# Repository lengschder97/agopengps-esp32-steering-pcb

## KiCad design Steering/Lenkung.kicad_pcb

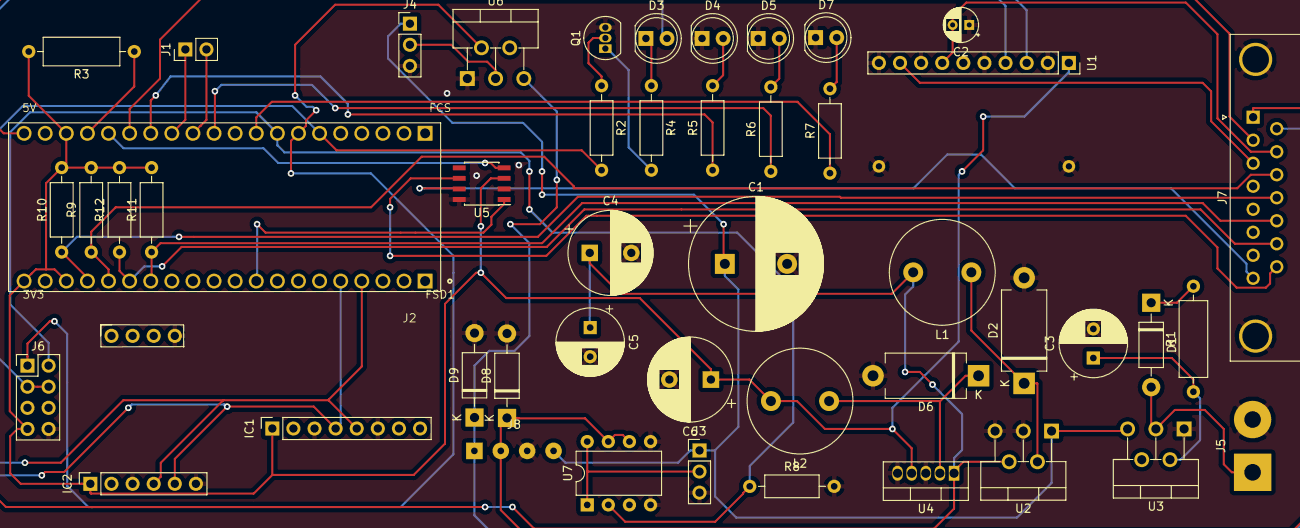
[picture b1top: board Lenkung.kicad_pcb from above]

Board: 2 copper layers, 47 parts (0 on the bottom side), 41 nets.

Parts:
C1: 680µF; CP_Radial_D16.0mm_P7.50mm
C2: 1OµF; CP_Radial_D4.0mm_P2.00mm
C3, C5: 100µF; CP_Radial_D8.0mm_P3.50mm
C4, C6: 220µF; CP_Radial_D10.0mm_P5.00mm
D1, D8, D9: 1N4007; D_DO-41_SOD81_P10.16mm_Horizontal
D2, D6: SB 530; D_DO-201_P12.70mm_Horizontal
D3, D4, D5, D7: LED; LED_D5.0mm
IC1: MMA8452-Board; PinSocket_1x08_P2.54mm_Vertical
IC2: BNO055; PinSocket_1x06_P2.54mm_Vertical-Board
J1: Conn_01x02_Female; PinHeader_1x02_P2.54mm_Vertical
J2: ESP32-PICO-KIT; XCVR_ESP32-PICO-KIT
J3, J4: Conn_01x03_Male; PinHeader_1x03_P2.54mm_Vertical
J5: Screw_Terminal_01x02; SolderWirePad_1x02_P7.62mm_Drill2mm
J6: Conn_02x04_Odd_Even; PinHeader_2x04_P2.54mm_Vertical
J7: DB15_Female_MountingHoles; DSUB-15_Female_Horizontal_P2.77x2.84mm_EdgePinOffset4.94mm_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
J8: Conn_01x04_Male; SolderWirePad_1x04_P3.175mm_Drill0.8mm
L1: L-09HCP 33µH; L_Radial_D12.5mm_P7.00mm_Fastron_09HCP
L2: L-09HVP 330µ; L_Radial_D12.5mm_P7.00mm_Fastron_09HCP
Q1: BC547; TO-92_Inline
R1: 1k; R_Axial_DIN0309_L9.0mm_D3.2mm_P12.70mm_Horizontal
R2: 5k6; R_Axial_DIN0207_L6.3mm_D2.5mm_P10.16mm_Horizontal
R3: 10k; R_Axial_DIN0309_L9.0mm_D3.2mm_P12.70mm_Horizontal
R4, R5, R6, R7: 330; R_Axial_DIN0207_L6.3mm_D2.5mm_P10.16mm_Horizontal
R8: 33k; R_Axial_DIN0207_L6.3mm_D2.5mm_P10.16mm_Horizontal
R9, R10, R11, R12: 10K; R_Axial_DIN0207_L6.3mm_D2.5mm_P10.16mm_Horizontal
U1: ADS1115-Adafruit; PinSocket_1x10_P2.54mm_Vertical_Board
U2: LM2596S-5; TO-220-5_P3.4x3.7mm_StaggerOdd_Lead3.8mm_Vertical
U3, U6: BTS432E2; TO-220-5_P3.4x3.7mm_StaggerOdd_Lead3.8mm_Vertical
U4: LM2575-3.3BT; TO-220-5_Vertical
U5: SN65HVD230; SOIC-8_3.9x4.9mm_P1.27mm
U7: MCP1407-E_P; DIP-8_W7.62mm

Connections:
+3V3: C6.1, IC1.1, IC2.1, J2.J2_18, J2.J2_20, J2.J3_18, J6.7, L2.2, R3.2, R9.2, R10.2, R11.2, R12.2, U1.1, U4.4, U5.3
+5V: C4.1, C5.1, D3.2, J2.J3_20, L1.2, U2.4, U4.1
+12V: C1.1, J3.1, J4.1, J8.4, U2.1, U3.5
AI: J2.J3_15, J7.2
Autosteer-EN: J2.J3_6, J6.3, J6.4, R2.2
CANH: J7.8, U5.7
CANL: J7.15, U5.6
CANRX: J2.J3_16, U5.4
CANTX: J2.J2_9, U5.1
Direction: J2.J3_7, J6.1, U6.2
EncoderA: J2.J2_14, J7.13, R11.1
EncoderB: J2.J2_15, J7.14, R12.1
GND: C1.2, C2.1, C3.2, C4.2, C5.2, C6.2, D2.2, D4.1, D5.1, D6.2, D7.1, D8.2, D9.2, IC1.3, IC1.6, IC2.3, IC2.6, IC2.7, J3.3, J4.3, J5.2, J6.8, J7.0, J8.3, Q1.3, R8.2, U1.2, U1.5, U1.8, U1.10, U2.3, U2.5, U3.1, U4.3, U4.5, U5.2, U5.8, U6.1, U7.4, U7.5
LED1: J2.J3_14, R5.1
LED2: J2.J3_11, R6.1
LED3: J2.J3_9, R7.1
Motor-Out1: D8.1, J7.1, J8.2, U7.6, U7.7
Motor-Out2: D9.1, J7.9, J8.1, U6.5
unnamed: C3.1, R1.1, U3.2
unnamed: D1.1, R1.2
unnamed: D2.1, L1.1, U2.2
unnamed: D3.1, R4.1
unnamed: D4.2, R5.2
unnamed: D5.2, R6.2
unnamed: D6.1, L2.1, U4.2
unnamed: D7.2, R7.2
unnamed: J1.1, J2.J3_13
unnamed: J1.2, J2.J3_12
unnamed: J2.J3_17, R3.1
unnamed: J3.2, U7.1, U7.8
unnamed: J4.2, U6.3
unnamed: Q1.1, R4.2
unnamed: Q1.2, R2.1
PWM: J2.J3_8, J6.2, R8.1, U7.2
SCL: IC1.4, IC2.5, J2.J2_5, U1.3
SDA: IC1.5, IC2.4, J2.J2_4, U1.4
SteerSW: J2.J2_16, J7.11, R9.1
V-Traktor: D1.2, J5.1, U3.3
WAS1: C2.2, J7.10, U1.7
WAS2: J7.3, U1.9
WorkSW: J2.J2_17, J7.12, R10.1
